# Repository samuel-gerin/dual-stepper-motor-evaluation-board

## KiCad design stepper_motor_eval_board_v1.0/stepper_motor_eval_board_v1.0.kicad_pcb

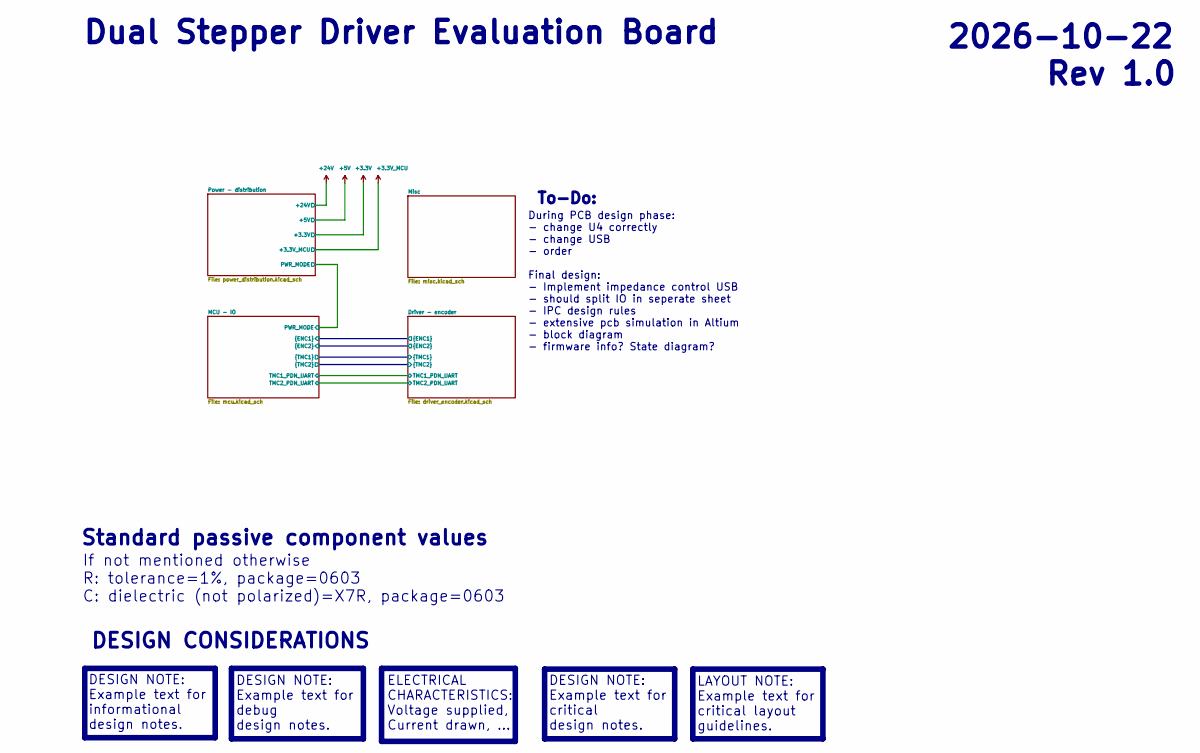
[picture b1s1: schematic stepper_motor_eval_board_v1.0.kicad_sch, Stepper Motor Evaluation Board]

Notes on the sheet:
Dual Stepper Driver Evaluation Board
ELECTRICAL CHARACTERISTICS: Voltage supplied, Current drawn, ...
During PCB design phase: - change U4 correctly - change USB - order Final design: - Implement impedance control USB - should split IO in seperate sheet - IPC design rules - extensive pcb simulation in Altium - block diagram - firmware info? State diagram?
To-Do:
2026-10-22
Rev 1.0
DESIGN NOTE: Example text for informational design notes.
DESIGN NOTE: Example text for critical design notes.
If not mentioned otherwise R: tolerance=1%, package=0603 C: dielectric (not polarized)=X7R, package=0603
DESIGN NOTE: Example text for debug design notes.
Standard passive component values
DESIGN CONSIDERATIONS
LAYOUT NOTE: Example text for critical layout guidelines.

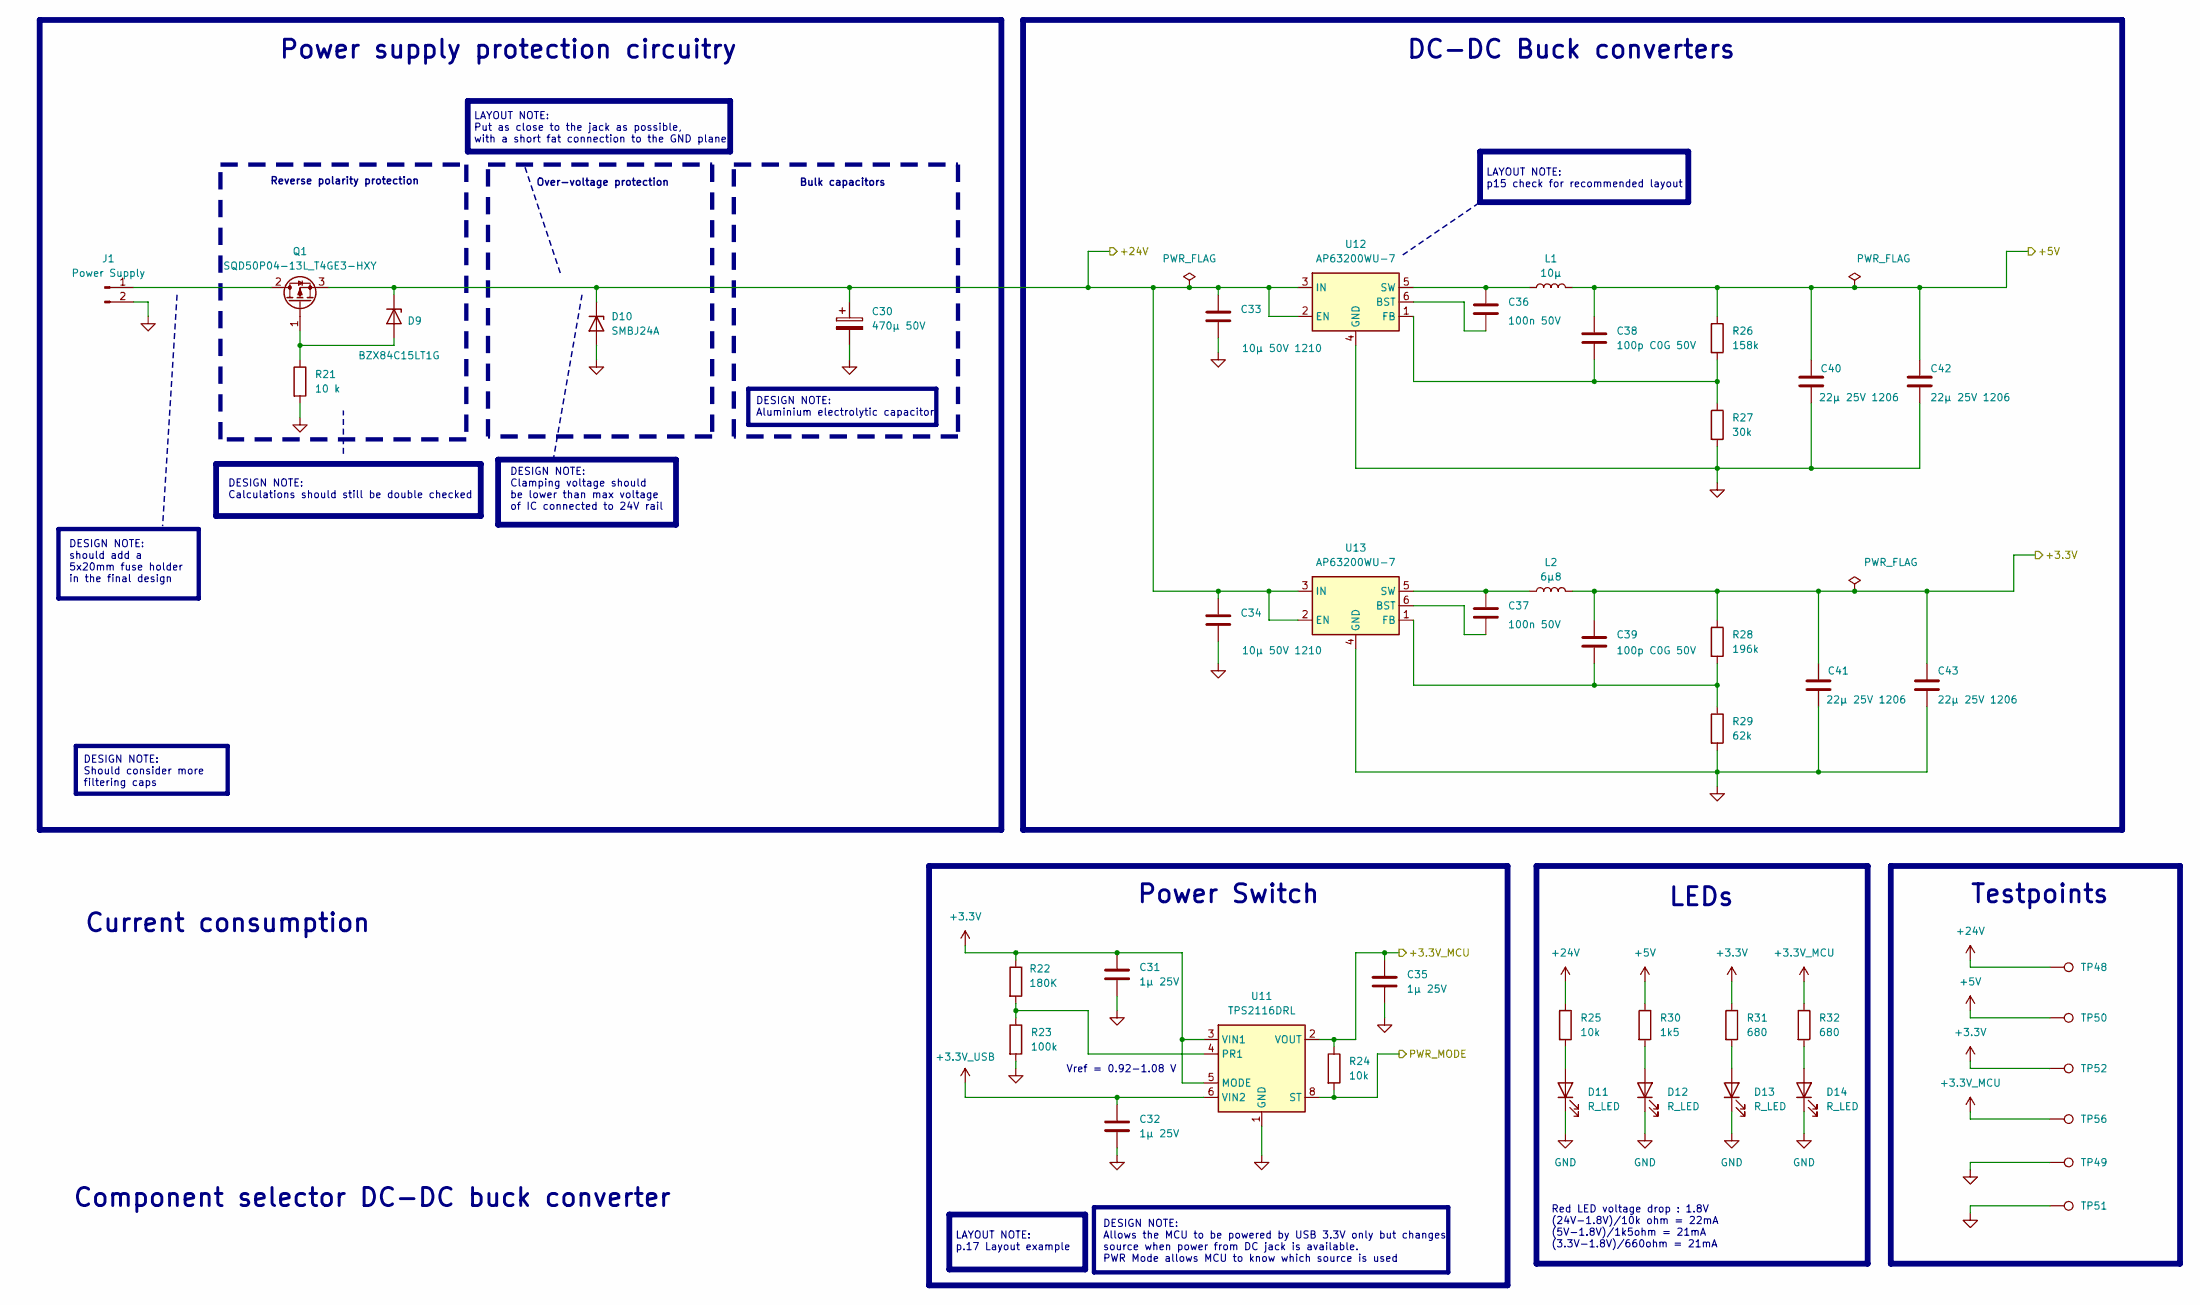
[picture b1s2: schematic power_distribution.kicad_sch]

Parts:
C30: 470µ 50V; CP_Elec_10x12.5; LCSC C22469994
C31, C32, C35: 1µ 25V; C_0603_1608Metric; LCSC C5673
C33, C34: 10µ 50V 1210; C_1210_3225Metric; LCSC C77102
C36, C37: 100n 50V; C_0603_1608Metric; LCSC C14663
C38, C39: 100p C0G 50V; C_0603_1608Metric; LCSC C14858
C40, C41, C42, C43: 22µ 25V 1206; C_1206_3216Metric; LCSC C12891
D9: BZX84C15LT1G; SOT-23; LCSC C80857
D10: SMBJ24A; D_SMB; LCSC C19077578
D11, D12, D13, D14: R_LED; LED_0603_1608Metric; LCSC C2286
J1: Power Supply; TerminalBlock_Phoenix_MKDS-1,5-2-5.08_1x02_P5.08mm_Horizont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
L1: 10µ; IND_ASPI-0630HI-3R3M-T15; LCSC C5949168
L2: 6µ8; IND_ASPI-0630HI-3R3M-T15; LCSC C2046638
Q1: SQD50P04-13L_T4GE3-HXY; TO-252-2; LCSC C49256455
R21: 10 k; R_0805_2012Metric; LCSC C17414
R22: 180K; R_0603_1608Metric; LCSC C22827
R23: 100k; R_0603_1608Metric; LCSC C25803
R24, R25: 10k; R_0603_1608Metric; LCSC C25804
R26: 158k; R_0603_1608Metric; LCSC C22883
R27: 30k; R_0603_1608Metric; LCSC C22984
R28: 196k; R_0603_1608Metric; LCSC C22930
R29: 62k; R_0603_1608Metric; LCSC C23221
R30: 1k5; R_0603_1608Metric; LCSC C22843
R31, R32: 680; R_0603_1608Metric; LCSC C23228
TP48, TP50, TP52, TP56: TestPoint; TestPoint_Keystone_5000_Miniature; LCSC C5199900
TP49, TP51: TestPoint; TestPoint_Keystone_5001_Miniature; LCSC C238122
U11: TPS2116DRL; SOT-583-8; LCSC C3235557
U12, U13: AP63200WU-7; TSOT-23-6; LCSC C2071868

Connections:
+3.3V: C31.1, C39.1, C41.1, C43.1, L2.2, R22.1, R28.1, R31.1, TP52.1 (1_1), U11.3 (VIN1), U11.5 (MODE); also elsewhere on the board
+3.3V_MCU: C35.1, R24.1, R32.1, TP56.1 (1_1), U11.2 (VOUT), U11.7 (VOUT); also elsewhere on the board
+3.3V_USB: C32.1, U11.6 (VIN2); also elsewhere on the board
+5V: C38.1, C40.1, C42.1, L1.2, R26.1, R30.1, TP50.1 (1_1); also elsewhere on the board
+24V: C30.1, C33.1, C34.1, D9.3 (K), D10.1 (K), Q1.3 (S), R25.1, TP48.1 (1_1), U12.2 (EN), U12.3 (IN), U13.2 (EN), U13.3 (IN); also elsewhere on the board
/MCU - IO/PWR_MODE: R24.2, U11.8 (ST); also elsewhere on the board
GND: C30.2, C31.2, C32.2, C33.2, C34.2, C35.2, C40.2, C41.2, C42.2, C43.2, D10.2 (A), D11.1 (K), D12.1 (K), D13.1 (K), D14.1 (K), J1.2, R21.2, R23.2, R27.2, R29.2, TP49.1 (1_1), TP51.1 (1_1), U11.1 (GND), U12.4 (GND), U13.4 (GND); also elsewhere on the board
unnamed: D9.1 (A), Q1.1 (G), R21.1
unnamed: D11.2 (A), R25.2
unnamed: D12.2 (A), R30.2
unnamed: D13.2 (A), R31.2
unnamed: D14.2 (A), R32.2
unnamed: J1.1, Q1.2 (D)
unnamed: R22.2, R23.1, U11.4 (PR1)
unnamed: C36.1, U12.6 (BST)
unnamed: C38.2, R26.2, R27.1, U12.1 (FB)
unnamed: C36.2, L1.1, U12.5 (SW)
unnamed: C37.1, U13.6 (BST)
unnamed: C39.2, R28.2, R29.1, U13.1 (FB)
unnamed: C37.2, L2.1, U13.5 (SW)

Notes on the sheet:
Red LED voltage drop : 1.8V (24V-1.8V)/10k ohm = 22mA (5V-1.8V)/1k5ohm = 21mA (3.3V-1.8V)/660ohm = 21mA
Reverse polarity protection
Power Switch
LEDs
Testpoints
LAYOUT NOTE: Put as close to the jack as possible, with a short fat connection to the GND plane
DESIGN NOTE: Calculations should still be double checked
DC-DC Buck converters
Over-voltage protection
Component selector DC-DC buck converter
Bulk capacitors
DESIGN NOTE: should add a 5x20mm fuse holder in the final design
LAYOUT NOTE: p15 check for recommended layout
DESIGN NOTE: Allows the MCU to be powered by USB 3.3V only but changes source when power from DC jack is available. PWR Mode allows MCU to know which source is used
DESIGN NOTE: Should consider more filtering caps
LAYOUT NOTE: p.17 Layout example
DESIGN NOTE: Aluminium electrolytic capacitor
Current consumption
Vref = 0.92-1.08 V
Power supply protection circuitry
DESIGN NOTE: Clamping voltage should be lower than max voltage of IC connected to 24V rail

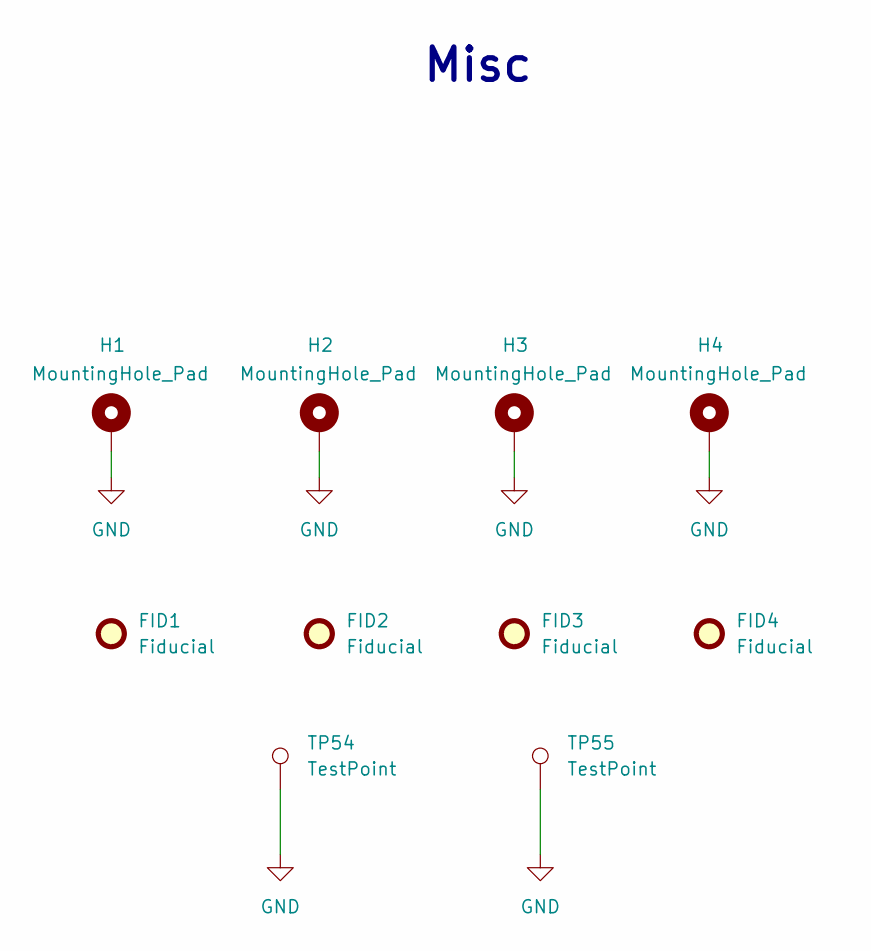
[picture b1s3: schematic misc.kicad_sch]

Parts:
FID1, FID2, FID3, FID4: Fiducial; Fiducial_1mm_Mask2mm
H1, H2, H3, H4: MountingHole_Pad; MountingHole_3.2mm_M3_Pad_Via
TP54, TP55: TestPoint; TestPoint_Keystone_5001_Miniature; LCSC C238122

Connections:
GND: H1.1 (1_1), H2.1 (1_1), H3.1 (1_1), H4.1 (1_1), TP54.1, TP55.1 (1_1); also elsewhere on the board

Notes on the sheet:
Misc

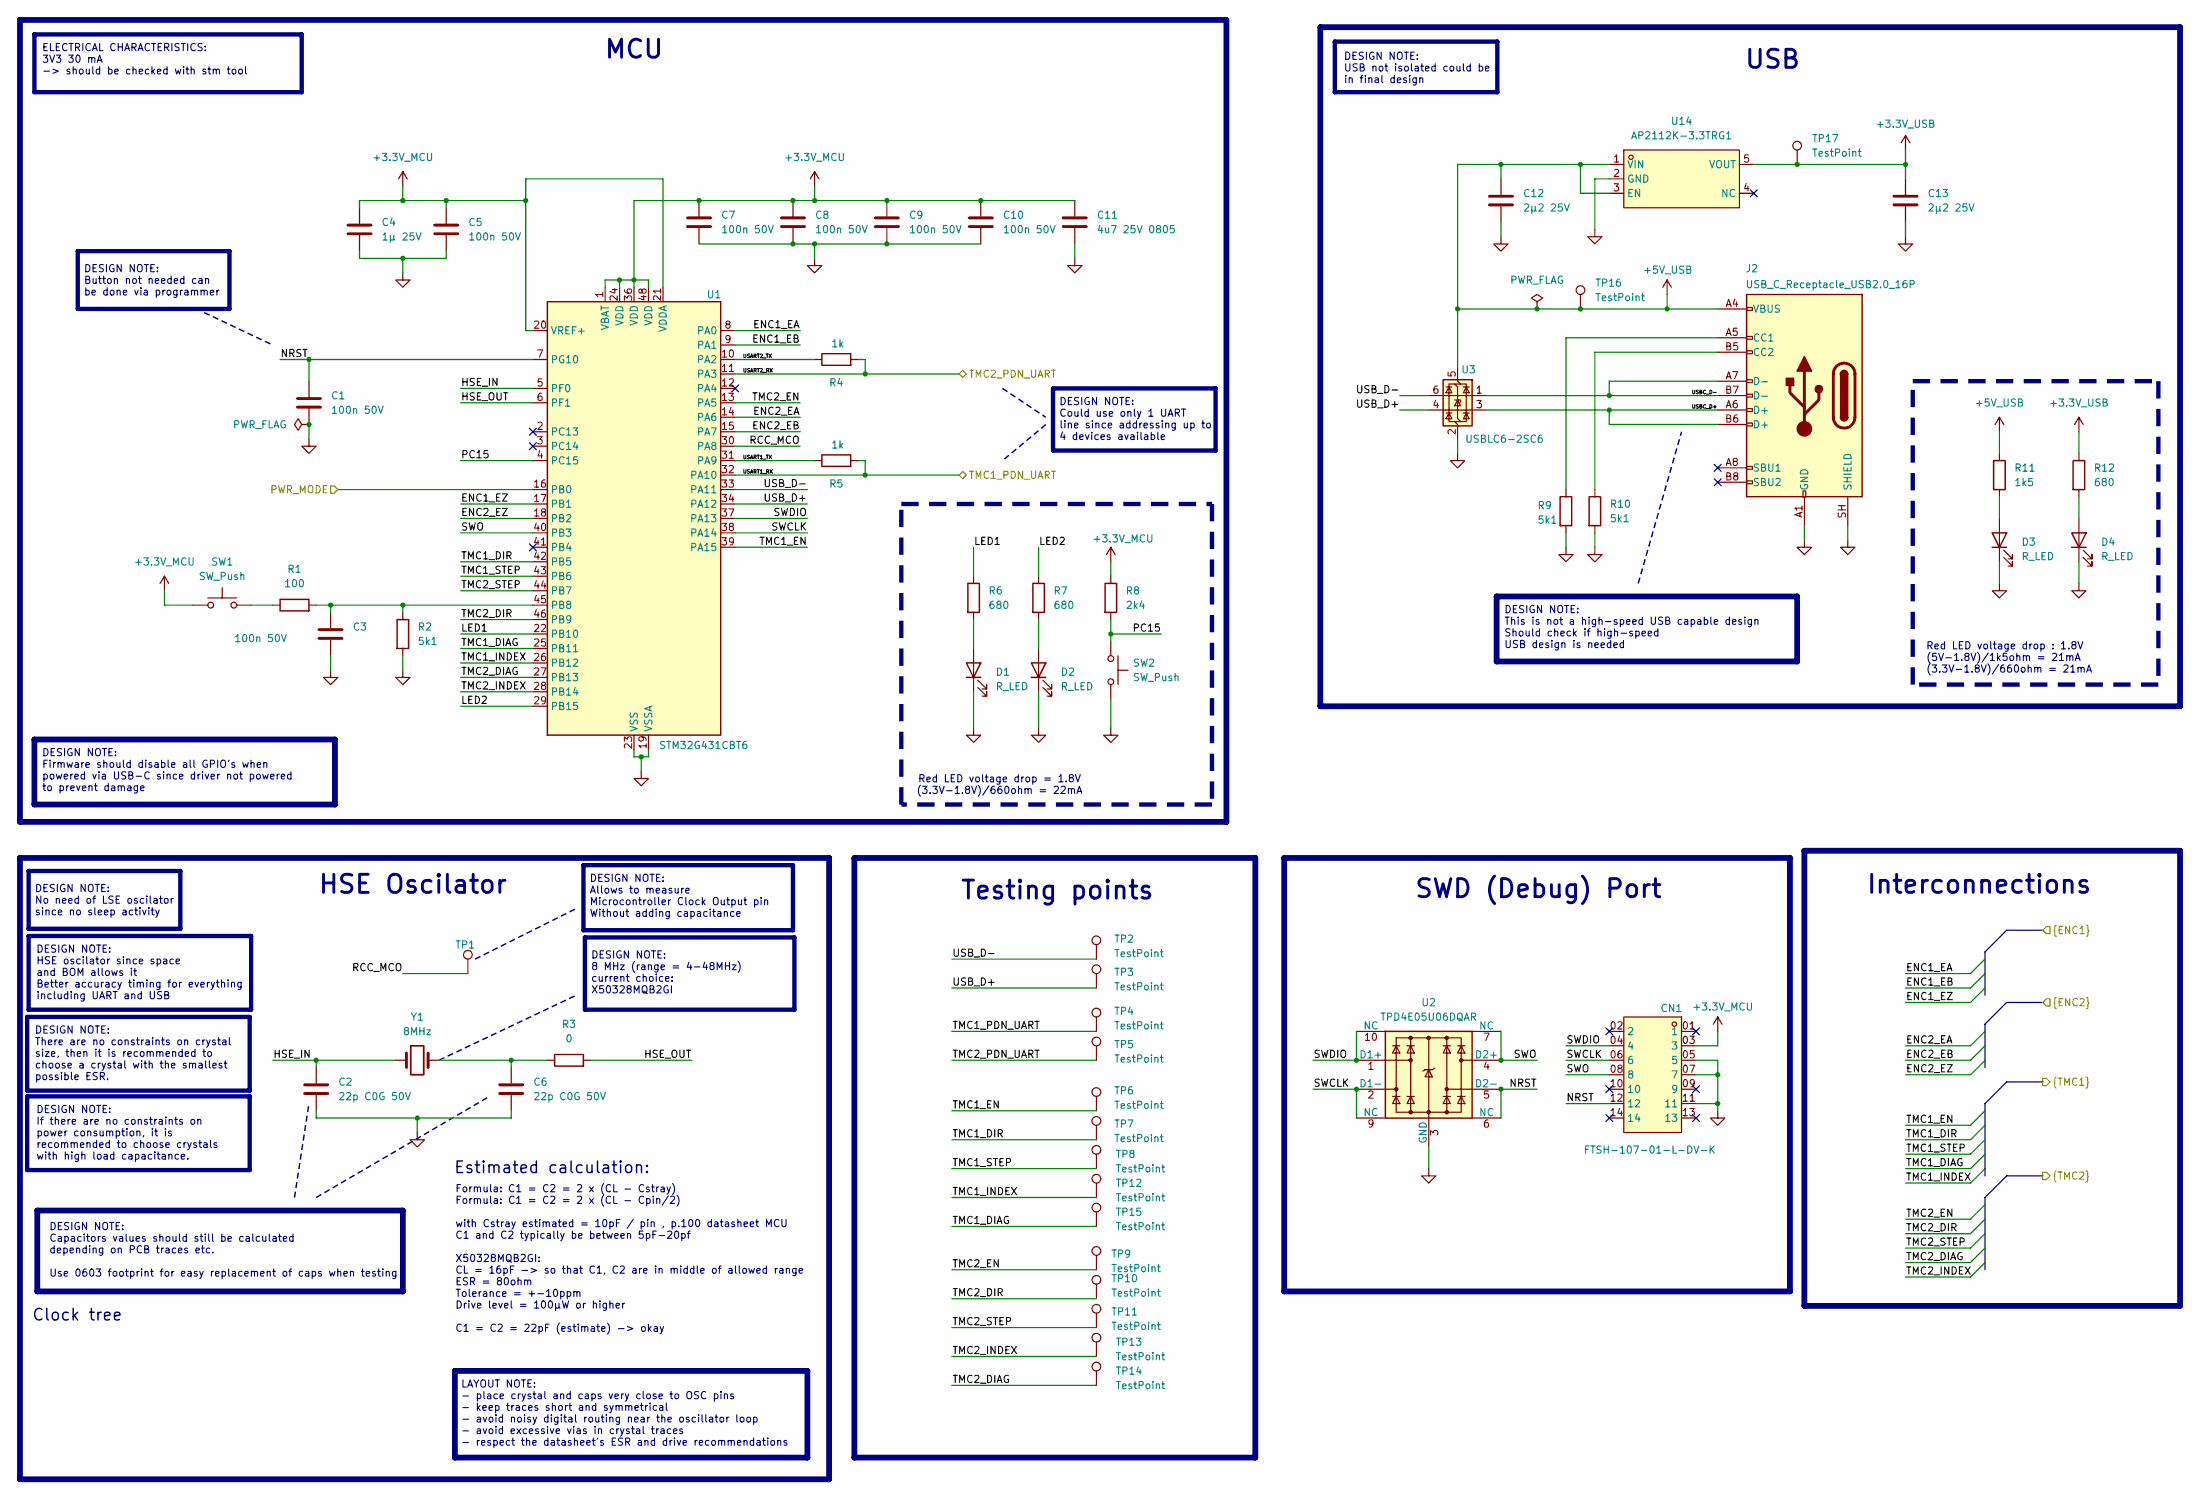
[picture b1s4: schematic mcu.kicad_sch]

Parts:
C1, C3, C5, C7, C8, C9, C10: 100n 50V; C_0603_1608Metric; LCSC C14663
C2, C6: 22p C0G 50V; C_0603_1608Metric; LCSC C1653
C4: 1µ 25V; C_0603_1608Metric; LCSC C5673
C11: 4u7 25V 0805; C_0805_2012Metric; LCSC C98195
C12, C13: 2µ2 25V; C_0603_1608Metric; LCSC C57895
CN1: FTSH-107-01-L-DV-K; HDR-SMD_14P-P1.27_FTSH-107-01-L-DV-K; MPN FTSH-107-01-L-DV-K; LCSC Part C5307809
D1, D2, D3, D4: R_LED; LED_0603_1608Metric; LCSC C2286
J2: USB_C_Receptacle_USB2.0_16P; USB_C_Receptacle_GCT_USB4105-xx-A_16P_TopMnt_Horizontal; LCSC C3020560
R1: 100; R_0603_1608Metric; LCSC C22775
R2, R9, R10: 5k1; R_0603_1608Metric; LCSC C23186
R3: 0; R_0603_1608Metric; LCSC C21189
R4, R5: 1k; R_0603_1608Metric; LCSC C21190
R6, R7, R12: 680; R_0603_1608Metric; LCSC C23228
R8: 2k4; R_0603_1608Metric; LCSC C22940
R11: 1k5; R_0603_1608Metric; LCSC C22843
SW1, SW2: SW_Push; KEY-SMD_4P-L6.0-W6.0-P4.50-LS8.6; LCSC C381044
TP1, TP2, TP3, TP4, TP5, TP6, TP7, TP8, TP9, TP10, TP11, TP12, TP13, TP14, TP15: TestPoint; TestPoint_Keystone_5002_Miniature; LCSC C238123
TP16, TP17: TestPoint; TestPoint_Keystone_5000_Miniature; LCSC C5199900
U1: STM32G431CBT6; LQFP-48_7x7mm_P0.5mm; LCSC C529355
U2: TPD4E05U06DQAR; USON-10_2.5x1.0mm_P0.5mm; LCSC C138714
U3: USBLC6-2SC6; SOT-23-6; LCSC C7519
U14: AP2112K-3.3TRG1; SOT-25-5_L2.9-W1.6-P0.95-LS2.8-BL; MPN AP2112K-3.3TRG1; LCSC Part C51118
Y1: 8MHz; Crystal_SMD_5032-2Pin_5.0x3.2mm; LCSC C20617998

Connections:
+3.3V_MCU: C4.1, C5.1, C7.1, C8.1, C9.1, C10.1, C11.1, CN1.03 (3), R8.1, SW1.1, U1.1 (VBAT), U1.20 (VREF+), U1.21 (VDDA), U1.24 (VDD), U1.36 (VDD), U1.48 (VDD); also elsewhere on the board
+3.3V_USB: C13.1, R12.1, TP17.1 (1_1), U14.5 (VOUT); also elsewhere on the board
+5V_USB: C12.1, J2.A4 (VBUS), J2.A9 (VBUS), J2.B4 (VBUS), J2.B9 (VBUS), R11.1, TP16.1 (1_1), U3.5 (VBUS), U14.1 (VIN), U14.3 (EN)
/Driver - encoder/ENC1_EA: U1.8 (PA0); also elsewhere on the board
/Driver - encoder/ENC1_EB: U1.9 (PA1); also elsewhere on the board
/Driver - encoder/ENC1_EZ: U1.17 (PB1); also elsewhere on the board
/Driver - encoder/ENC2_EA: U1.14 (PA6); also elsewhere on the board
/Driver - encoder/ENC2_EB: U1.15 (PA7); also elsewhere on the board
/Driver - encoder/ENC2_EZ: U1.18 (PB2); also elsewhere on the board
/Driver - encoder/TMC1_DIAG: TP15.1 (1_1), U1.25 (PB11); also elsewhere on the board
/Driver - encoder/TMC1_DIR: TP7.1 (1_1), U1.42 (PB5); also elsewhere on the board
/Driver - encoder/TMC1_EN: TP6.1 (1_1), U1.39 (PA15); also elsewhere on the board
/Driver - encoder/TMC1_INDEX: TP12.1 (1_1), U1.26 (PB12); also elsewhere on the board
/Driver - encoder/TMC1_STEP: TP8.1 (1_1), U1.43 (PB6); also elsewhere on the board
/Driver - encoder/TMC2_DIAG: TP14.1 (1_1), U1.27 (PB13); also elsewhere on the board
/Driver - encoder/TMC2_DIR: TP10.1 (1_1), U1.46 (PB9); also elsewhere on the board
/Driver - encoder/TMC2_EN: TP9.1 (1_1), U1.13 (PA5); also elsewhere on the board
/Driver - encoder/TMC2_INDEX: TP13.1 (1_1), U1.28 (PB14); also elsewhere on the board
/Driver - encoder/TMC2_STEP: TP11.1 (1_1), U1.44 (PB7); also elsewhere on the board
/MCU - IO/HSE_IN: C2.1, U1.5 (PF0), Y1.1
/MCU - IO/HSE_OUT: R3.2, U1.6 (PF1)
/MCU - IO/LED1: R6.1, U1.22 (PB10)
/MCU - IO/LED2: R7.1, U1.29 (PB15)
/MCU - IO/NRST: C1.1, CN1.12, U1.7 (PG10), U2.5 (D2-), U2.6 (NC)
/MCU - IO/PC15: R8.2, SW2.1, U1.4 (PC15)
/MCU - IO/PWR_MODE: U1.16 (PB0); also elsewhere on the board
/MCU - IO/RCC_MCO: TP1.1 (1_1), U1.30 (PA8)
/MCU - IO/SWCLK: CN1.06 (6), U1.38 (PA14), U2.2 (D1-), U2.9 (NC)
/MCU - IO/SWDIO: CN1.04 (4), U1.37 (PA13), U2.1 (D1+), U2.10 (NC)
/MCU - IO/SWO: CN1.08 (8), U1.40 (PB3), U2.4 (D2+), U2.7 (NC)
/MCU - IO/TMC1_PDN_UART: R5.2, TP4.1 (1_1), U1.32 (PA10); also elsewhere on the board
/MCU - IO/TMC2_PDN_UART: R4.2, TP5.1 (1_1), U1.11 (PA3); also elsewhere on the board
/MCU - IO/USART1_TX: R5.1, U1.31 (PA9)
/MCU - IO/USART2_TX: R4.1, U1.10 (PA2)
/MCU - IO/USBC_D+: J2.A6 (D+), J2.B6 (D+), U3.3 (I/O2)
/MCU - IO/USBC_D-: J2.A7 (D-), J2.B7 (D-), U3.1 (I/O1)
/MCU - IO/USB_D+: TP3.1 (1_1), U1.34 (PA12), U3.4 (I/O2)
/MCU - IO/USB_D-: TP2.1 (1_1), U1.33 (PA11), U3.6 (I/O1)
GND: C1.2, C2.2, C3.2, C4.2, C5.2, C6.2, C7.2, C8.2, C9.2, C10.2, C11.2, C12.2, C13.2, CN1.05 (5), CN1.07 (7), CN1.11, D1.1 (K), D2.1 (K), D3.1 (K), D4.1 (K), J2.A1 (GND), J2.A12 (GND), J2.B1 (GND), J2.B12 (GND), J2.SH (SHIELD), R2.2, R9.2, R10.2, SW2.2, U1.19 (VSSA), U1.23 (VSS), U1.35 (VSS), U1.47 (VSS), U2.3 (GND), U2.8 (GND), U3.2 (GND), U14.2 (GND); also elsewhere on the board
unnamed: C6.1, R3.1, Y1.2
unnamed: D1.2 (A), R6.2
unnamed: D2.2 (A), R7.2
unnamed: D3.2 (A), R11.2
unnamed: D4.2 (A), R12.2
unnamed: J2.A5 (CC1), R9.1
unnamed: J2.B5 (CC2), R10.1
unnamed: R1.1, SW1.2
unnamed: C3.1, R1.2, R2.1, U1.45 (PB8)

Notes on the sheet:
Clock tree
USB
Testing points
DESIGN NOTE: This is not a high-speed USB capable design Should check if high-speed USB design is needed
SWD (Debug) Port
DESIGN NOTE: Capacitors values should still be calculated depending on PCB traces etc. Use 0603 footprint for easy replacement of caps when testing
DESIGN NOTE: No need of LSE oscilator since no sleep activity
Red LED voltage drop = 1.8V (3.3V-1.8V)/660ohm = 22mA
DESIGN NOTE: Firmware should disable all GPIO's when powered via USB-C since driver not powered to prevent damage
HSE Oscilator
DESIGN NOTE: USB not isolated could be in final design
DESIGN NOTE: There are no constraints on crystal size, then it is recommended to choose a crystal with the smallest possible ESR.
DESIGN NOTE: 8 MHz (range = 4-48MHz) current choice: X50328MQB2GI
DESIGN NOTE: Button not needed can be done via programmer
Interconnections
LAYOUT NOTE: - place crystal and caps very close to OSC pins - keep traces short and symmetrical - avoid noisy digital routing near the oscillator loop - avoid excessive vias in crystal traces - respect the datasheet's ESR and drive recommendations
DESIGN NOTE: Allows to measure Microcontroller Clock Output pin Without adding capacitance
Red LED voltage drop : 1.8V (5V-1.8V)/1k5ohm = 21mA (3.3V-1.8V)/660ohm = 21mA
Formula: C1 = C2 = 2 x (CL - Cstray) Formula: C1 = C2 = 2 x (CL - Cpin/2) with Cstray estimated = 10pF / pin , p.100 datasheet MCU C1 and C2 typically be between 5pF-20pf X50328MQB2GI: CL = 16pF -> so that C1, C2 are in middle of allowed range ESR = 80ohm Tolerance = +-10ppm Drive level = 100µW or 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
MCU
Estimated calculation:
DESIGN NOTE: If there are no constraints on power consumption, it is recommended to choose crystals with high load capacitance.
DESIGN NOTE: Could use only 1 UART line since addressing up to 4 devices available
ELECTRICAL CHARACTERISTICS: 3V3 30 mA -> should be checked with stm tool
DESIGN NOTE: HSE oscilator since space and BOM allows it Better accuracy timing for everything including UART and USB

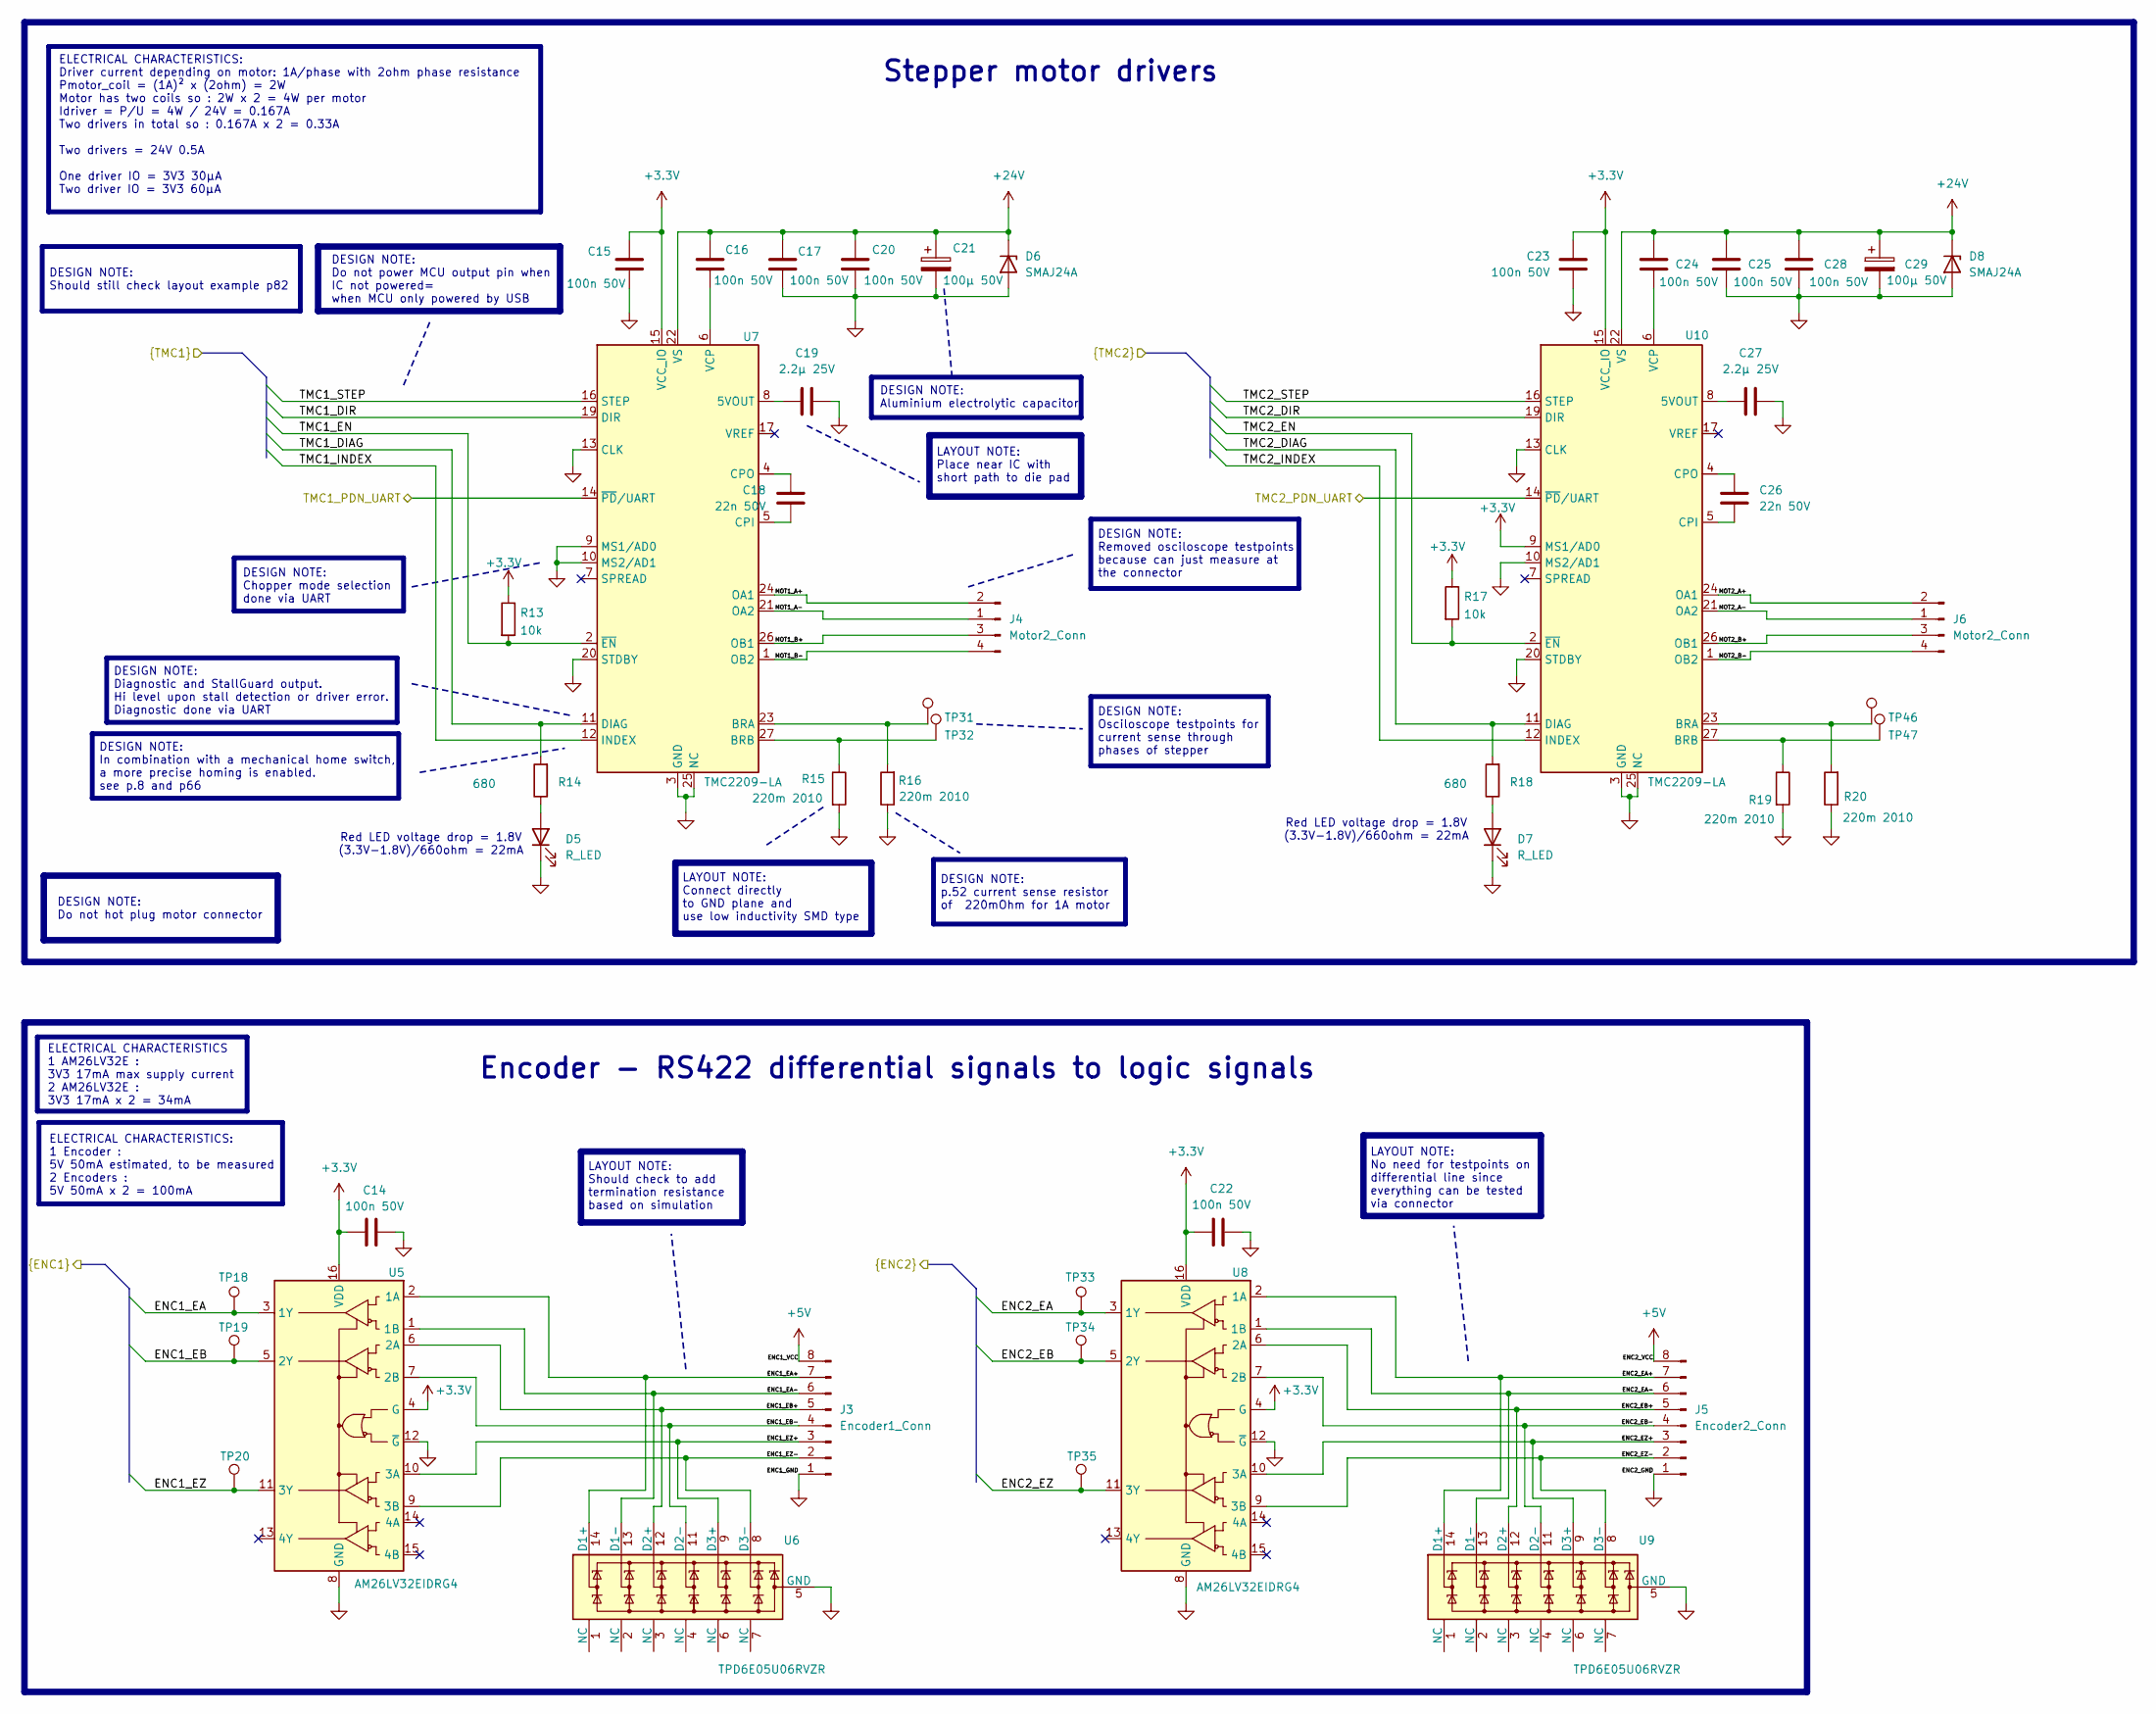
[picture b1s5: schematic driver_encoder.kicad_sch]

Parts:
C14, C15, C16, C17, C20, C22, C23, C24, C25, C28: 100n 50V; C_0603_1608Metric; LCSC C14663
C18, C26: 22n 50V; C_0603_1608Metric; LCSC C21122
C19, C27: 2.2µ 25V; C_0603_1608Metric; LCSC C99228
C21, C29: 100µ 50V; CP_Elec_6.3x7.7; LCSC C962164
D5, D7: R_LED; LED_0603_1608Metric; LCSC C2286
D6, D8: SMAJ24A; D_SMA; LCSC C19077541
J3: Encoder1_Conn; TerminalBlock_Phoenix_MKDS-1,5-8-5.08_1x08_P5.08mm_Horizont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
J4, J6: Motor2_Conn; TerminalBlock_Phoenix_MKDS-1,5-4-5.08_1x04_P5.08mm_Horizont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
J5: Encoder2_Conn; TerminalBlock_Phoenix_MKDS-1,5-8-5.08_1x08_P5.08mm_Horizont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
R13, R17: 10k; R_0603_1608Metric; LCSC C25804
R14, R18: 680; R_0603_1608Metric; LCSC C23228
R15, R16, R19, R20: 220m 2010; R_2010_5025Metric; LCSC C146381
TP18, TP19, TP20, TP31, TP32, TP33, TP34, TP35, TP46, TP47: TestPoint; TestPoint_Keystone_5002_Miniature; LCSC C238123
U5, U8: AM26LV32EIDRG4; SOIC-16_3.9x9.9mm_P1.27mm; LCSC C527448
U6, U9: TPD6E05U06RVZR; Texas_R-PUSON-N14; LCSC C962978
U7, U10: TMC2209-LA; VQFN-28-1EP_5x5mm_P0.5mm_EP3.7x3.7mm_ThermalVias; LCSC C2150710

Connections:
+3.3V: C14.1, C15.1, C22.1, C23.1, R13.1, R17.1, U5.4 (G), U5.16 (VDD), U7.15 (VCC_IO), U8.4 (G), U8.16 (VDD), U10.9 (MS1/AD0), U10.15 (VCC_IO); also elsewhere on the board
+5V: J3.8, J5.8; also elsewhere on the board
+24V: C16.1, C17.1, C20.1, C21.1, C24.1, C25.1, C28.1, C29.1, D6.1 (K), D8.1 (K), U7.22 (VS), U7.28 (VS), U10.22 (VS), U10.28 (VS); also elsewhere on the board
/Driver - encoder/ENC1_EA: TP18.1 (1_1), U5.3 (1Y); also elsewhere on the board
/Driver - encoder/ENC1_EA+: J3.7, U5.2 (1A), U6.1 (NC), U6.14 (D1+)
/Driver - encoder/ENC1_EA-: J3.6, U5.1 (1B), U6.2 (NC), U6.13 (D1-)
/Driver - encoder/ENC1_EB: TP19.1 (1_1), U5.5 (2Y); also elsewhere on the board
/Driver - encoder/ENC1_EB+: J3.5, U5.6 (2A), U6.3 (NC), U6.12 (D2+)
/Driver - encoder/ENC1_EB-: J3.4, U5.7 (2B), U6.4 (NC), U6.11 (D2-)
/Driver - encoder/ENC1_EZ: TP20.1 (1_1), U5.11 (3Y); also elsewhere on the board
/Driver - encoder/ENC1_EZ+: J3.3, U5.10 (3A), U6.6 (NC), U6.9 (D3+)
/Driver - encoder/ENC1_EZ-: J3.2, U5.9 (3B), U6.7 (NC), U6.8 (D3-)
/Driver - encoder/ENC2_EA: TP33.1 (1_1), U8.3 (1Y); also elsewhere on the board
/Driver - encoder/ENC2_EA+: J5.7, U8.2 (1A), U9.1 (NC), U9.14 (D1+)
/Driver - encoder/ENC2_EA-: J5.6, U8.1 (1B), U9.2 (NC), U9.13 (D1-)
/Driver - encoder/ENC2_EB: TP34.1 (1_1), U8.5 (2Y); also elsewhere on the board
/Driver - encoder/ENC2_EB+: J5.5, U8.6 (2A), U9.3 (NC), U9.12 (D2+)
/Driver - encoder/ENC2_EB-: J5.4, U8.7 (2B), U9.4 (NC), U9.11 (D2-)
/Driver - encoder/ENC2_EZ: TP35.1 (1_1), U8.11 (3Y); also elsewhere on the board
/Driver - encoder/ENC2_EZ+: J5.3, U8.10 (3A), U9.6 (NC), U9.9 (D3+)
/Driver - encoder/ENC2_EZ-: J5.2, U8.9 (3B), U9.7 (NC), U9.8 (D3-)
/Driver - encoder/MOT1_A+: J4.2 (Pin_4), U7.24 (OA1)
/Driver - encoder/MOT1_A-: J4.1 (Pin_3), U7.21 (OA2)
/Driver - encoder/MOT1_B+: J4.3 (Pin_2), U7.26 (OB1)
/Driver - encoder/MOT1_B-: J4.4 (Pin_1), U7.1 (OB2)
/Driver - encoder/MOT2_A+: J6.2 (Pin_4), U10.24 (OA1)
/Driver - encoder/MOT2_A-: J6.1 (Pin_3), U10.21 (OA2)
/Driver - encoder/MOT2_B+: J6.3 (Pin_2), U10.26 (OB1)
/Driver - encoder/MOT2_B-: J6.4 (Pin_1), U10.1 (OB2)
/Driver - encoder/TMC1_DIAG: R14.2, U7.11 (DIAG); also elsewhere on the board
/Driver - encoder/TMC1_DIR: U7.19 (DIR); also elsewhere on the board
/Driver - encoder/TMC1_EN: R13.2, U7.2 (~EN); also elsewhere on the board
/Driver - encoder/TMC1_INDEX: U7.12 (INDEX); also elsewhere on the board
/Driver - encoder/TMC1_STEP: U7.16 (STEP); also elsewhere on the board
/Driver - encoder/TMC2_DIAG: R18.2, U10.11 (DIAG); also elsewhere on the board
/Driver - encoder/TMC2_DIR: U10.19 (DIR); also elsewhere on the board
/Driver - encoder/TMC2_EN: R17.2, U10.2 (~EN); also elsewhere on the board
/Driver - encoder/TMC2_INDEX: U10.12 (INDEX); also elsewhere on the board
/Driver - encoder/TMC2_STEP: U10.16 (STEP); also elsewhere on the board
/MCU - IO/TMC1_PDN_UART: U7.14 (~PD/UART); also elsewhere on the board
/MCU - IO/TMC2_PDN_UART: U10.14 (~PD/UART); also elsewhere on the board
GND: C14.2, C15.2, C17.2, C19.1, C20.2, C21.2, C22.2, C23.2, C25.2, C27.2, C28.2, C29.2, D5.1 (K), D6.2 (A), D7.1 (K), D8.2 (A), J3.1, J5.1, R15.2, R16.1, R19.2, R20.1, U5.8 (GND), U5.12 (~G), U6.5 (GND), U6.10 (GND), U7.3 (GND), U7.9 (MS1/AD0), U7.10 (MS2/AD1), U7.13 (CLK), U7.18 (GND), U7.20 (STDBY), U7.25 (NC), U7.29 (GND), U8.8 (GND), U8.12 (~G), U9.5 (GND), U9.10 (GND), U10.3 (GND), U10.10 (MS2/AD1), U10.13 (CLK), U10.18 (GND), U10.20 (STDBY), U10.25 (NC), U10.29 (GND); also elsewhere on the board
unnamed: D5.2 (A), R14.1
unnamed: D7.2 (A), R18.1
unnamed: C19.2, U7.8 (5VOUT)
unnamed: R16.2, TP31.1 (1_1), U7.23 (BRA)
unnamed: R15.1, TP32.1 (1_1), U7.27 (BRB)
unnamed: C18.2, U7.5 (CPI)
unnamed: C18.1, U7.4 (CPO)
unnamed: C16.2, U7.6 (VCP)
unnamed: C27.1, U10.8 (5VOUT)
unnamed: R20.2, TP46.1 (1_1), U10.23 (BRA)
unnamed: R19.1, TP47.1 (1_1), U10.27 (BRB)
unnamed: C26.2, U10.5 (CPI)
unnamed: C26.1, U10.4 (CPO)
unnamed: C24.2, U10.6 (VCP)

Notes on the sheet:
DESIGN NOTE: Diagnostic and StallGuard output. Hi level upon stall detection or driver error. Diagnostic done via UART
DESIGN NOTE: p.52 current sense resistor of 220mOhm for 1A motor
Encoder - RS422 differential signals to logic signals
DESIGN NOTE: In combination with a mechanical home switch, a more precise homing is enabled. see p.8 and p66
DESIGN NOTE: Removed osciloscope testpoints because can just measure at the connector
DESIGN NOTE: Aluminium electrolytic capacitor
DESIGN NOTE: Osciloscope testpoints for current sense through phases of stepper
LAYOUT NOTE: Place near IC with short path to die pad
ELECTRICAL CHARACTERISTICS 1 AM26LV32E : 3V3 17mA max supply current 2 AM26LV32E : 3V3 17mA x 2 = 34mA
LAYOUT NOTE: Should check to add termination resistance based on simulation
Red LED voltage drop = 1.8V (3.3V-1.8V)/660ohm = 22mA
DESIGN NOTE: Do not hot plug motor connector
DESIGN NOTE: Should still check layout example p82
LAYOUT NOTE: No need for testpoints on differential line since everything can be tested via connector
DESIGN NOTE: Chopper mode selection done via UART
ELECTRICAL CHARACTERISTICS: Driver current depending on motor: 1A/phase with 2ohm phase resistance Pmotor_coil = (1A)² x (2ohm) = 2W Motor has two coils so : 2W x 2 = 4W per motor Idriver = P/U = 4W / 24V = 0.167A Two drivers in total so : 0.167A x 2 = 0.33A Two drivers = 24V 0.5A One driver IO = 3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
ELECTRICAL CHARACTERISTICS: 1 Encoder : 5V 50mA estimated, to be measured 2 Encoders : 5V 50mA x 2 = 100mA
DESIGN NOTE: Do not power MCU output pin when IC not powered= when MCU only powered by USB
LAYOUT NOTE: Connect directly to GND plane and use low inductivity SMD type
Stepper motor drivers
